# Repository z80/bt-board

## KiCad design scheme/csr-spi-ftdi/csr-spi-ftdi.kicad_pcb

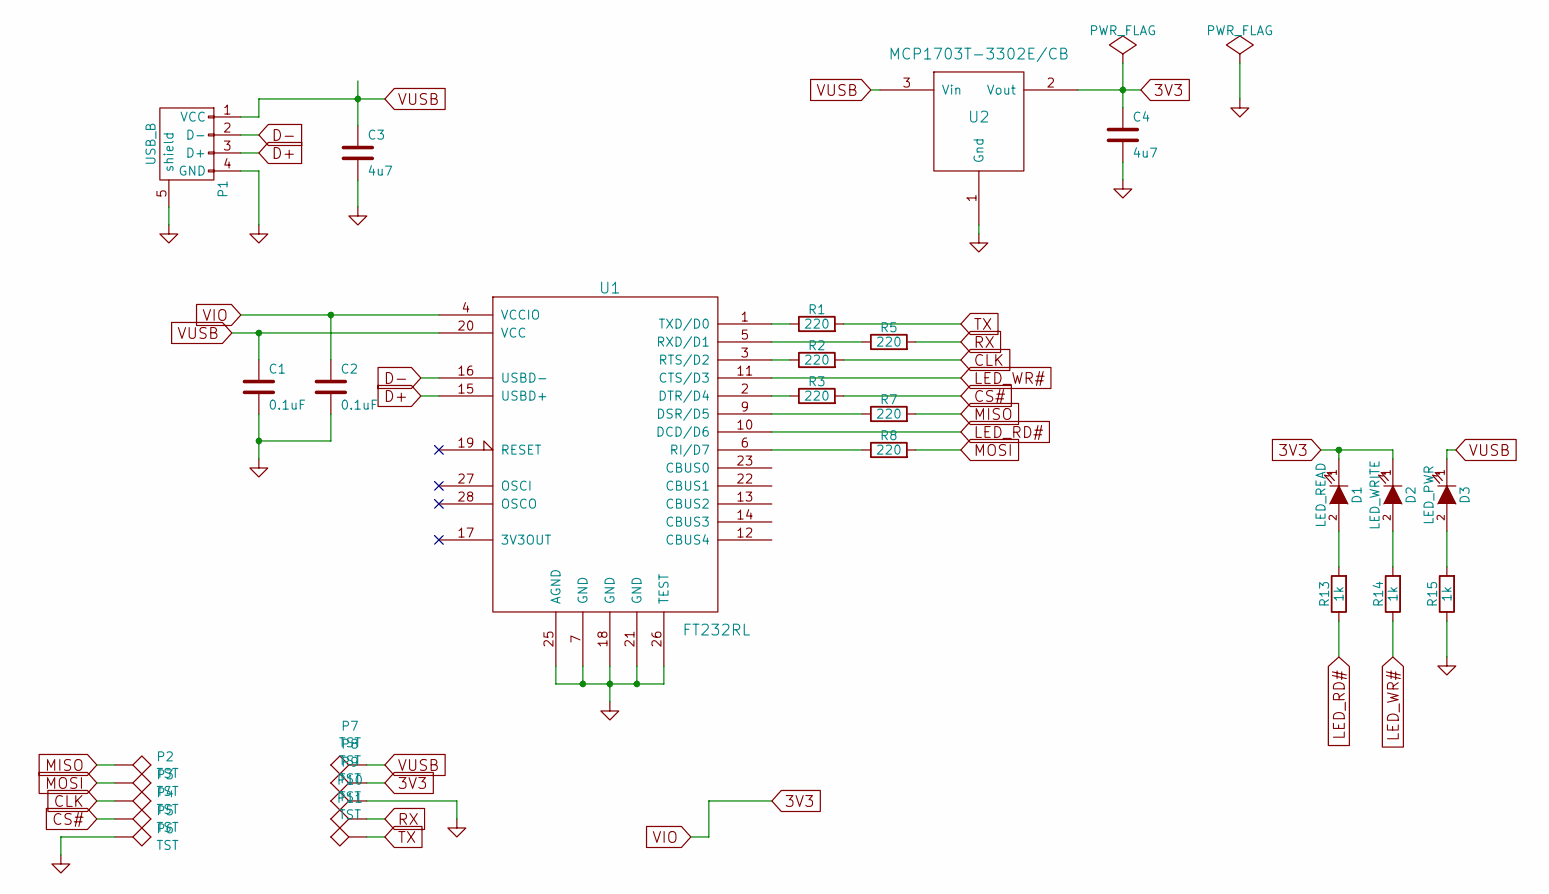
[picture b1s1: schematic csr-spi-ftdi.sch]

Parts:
C1, C2: 0.1uF; C_0805
C3, C4: 4u7; C_0805
D1: LED_READ; LED-5MM
D2: LED_WRITE; LED-5MM
D3: LED_PWR; LED-5MM
P1: USB_B
P2, P3, P4, P5, P6, P7, P8, P9, P10, P11: TST; Measurement_Point_Round-SMD-Pad_Small
R1, R2, R3, R5, R7, R8: 220; R_0805
R13, R14, R15: 1k; R_0805
U1: FT232RL; SSOP-28_5.3x10.2mm_Pitch0.65mm
U2: MCP1703T-3302E/CB; SOT-23_Handsoldering

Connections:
3V3: C2.1, C4.1, D1.1 (K), D2.1 (K), P8.1, U1.4 (VCCIO), U2.2 (Vout)
CLK: P4.1, R2.2
CS#: P5.1, R3.2
D+: P1.3 (D+), U1.15 (USBD+)
D-: P1.2 (D-), U1.16 (USBD-)
GND: C1.2, C2.2, C3.2, C4.2, P1.4 (GND), P1.5 (shield), P6.1, P9.1, R15.1, U1.7 (GND), U1.18 (GND), U1.21 (GND), U1.25 (AGND), U1.26 (TEST), U2.1 (Gnd)
LED_RD#: R13.1, U1.10 (DCD/D6)
LED_WR#: R14.1, U1.11 (CTS/D3)
MISO: P2.1, R7.2
MOSI: P3.1, R8.2
unnamed: D1.2 (A), R13.2
unnamed: D2.2 (A), R14.2
unnamed: D3.2 (A), R15.2
unnamed: R1.1, U1.1 (TXD/D0)
unnamed: R2.1, U1.3 (RTS/D2)
unnamed: R3.1, U1.2 (DTR/D4)
unnamed: R5.1, U1.5 (RXD/D1)
unnamed: R7.1, U1.9 (DSR/D5)
unnamed: R8.1, U1.6 (RI/D7)
RX: P10.1, R5.2
TX: P11.1, R1.2
VUSB: C1.1, C3.1, D3.1 (K), P1.1 (VCC), P7.1, U1.20 (VCC), U2.3 (Vin)

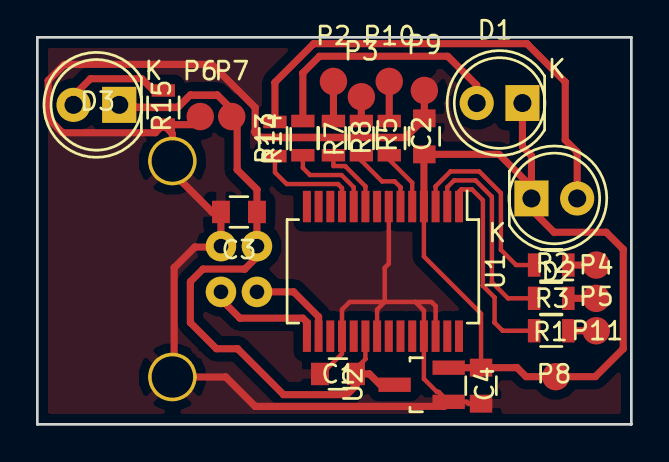
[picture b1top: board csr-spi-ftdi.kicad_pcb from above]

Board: 2 copper layers, 33.0 x 21.5 mm, 29 parts (1 on the bottom side), 22 nets.

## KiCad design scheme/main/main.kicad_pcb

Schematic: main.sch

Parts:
C1, C2: 18p
C3, C4, C6, C7, C8: 100n
C5, C10: 10u
C9: 100u
D1: LED
D2, D3: DIODE
J1: USB_A
K1: swd
P1: mode
P2: rst
P3, P5: CONN_20X2_F
P4, P7: CONN_20X2_M
P6: +
P8: -
R1: 100
R2, R3, R6, R7, R8, R9: 10k
R4, R5: 1k
R10: 100k
R11, R12: 22
R13: 1k5
U1: CRYSTAL-4PIN
U2: MCP1703T-3302E/CB
U3: MICRO-USB-B
stm1: STM32F102C8T6

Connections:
/Vin: D2.1 (A), P3.39, P3.40, P4.39, P4.40, P5.39, P5.40, P6.1, P7.39, P7.40
/Vusb: D3.1 (A), J1.1 (VCC), P3.37, P3.38, P4.37, P4.38, P5.37, P5.38, P7.37, P7.38, U3.1
/pa0: P3.3, P3.4, P4.3, P4.4, stm1.10 (PA0/WKUP/USART2_CTS/ADC_IN0/TIM2_CH1_ETR)
/pa1: P3.5, P3.6, P4.5, P4.6, stm1.11 (PA1/USART2_RTS/ADC_IN1/TIM2_CH2)
/pa2: P3.7, P3.8, P4.7, P4.8, stm1.12 (PA2/USART2_TX/ADC_IN2/TIM2_CH3)
/pa3: P3.9, P3.10, P4.9, P4.10, stm1.13 (PA3/USART2_RX/ADC_IN3/TIM2_CH4)
/pa4: P3.11, P3.12, P4.11, P4.12, stm1.14 (PA4/SPI1_NSS/ADC_IN4/USART2_CK)
/pa5: P3.13, P3.14, P4.13, P4.14, stm1.15 (PA5/SPI1_SCK/ADC_IN5)
/pa6: P3.15, P3.16, P4.15, P4.16, stm1.16 (PA6/SPI1_MISO/ADC_IN6/TIM3_CH1)
/pa7: P3.17, P3.18, P4.17, P4.18, stm1.17 (PA7/SPI1_MOSI/ADC_IN7/TIM3_CH2)
/pa8: P3.19, P3.20, P4.19, P4.20, stm1.29 (PA8/USART1_CK/MCO)
/pa9: P3.21, P3.22, P4.21, P4.22, stm1.30 (PA9/USART1_TX)
/pa10: P3.23, P3.24, P4.23, P4.24, stm1.31 (PA10/USART1_RX)
/pa15: P3.25, P3.26, P4.25, P4.26, stm1.38 (JDI^TIM2_CH1_ETR/PA15/SPI1_NSS)
/pb0: P3.27, P3.28, P4.27, P4.28, stm1.18 (PB0/ADC_IN8/TIM3_CH3)
/pb3: P3.29, P3.30, P4.29, P4.30, stm1.39 (JTDO^TIM2_CH2/PB3/TRACESWO/SPI1_SCKPB3)
/pb4: P3.31, P3.32, P4.31, P4.32, stm1.40 (JNTRST^TIM3_CH1/PB4/SPI1_MISO)
/pb5: P5.7, P5.8, P7.7, P7.8, stm1.41 (PB5/I2C1_SMBA^TIM3_CH2/SPI1_MOSI)
/pb6-scl1: P5.3, P5.4, P7.3, P7.4, R6.2, stm1.42 (PB6/I2C1_SCL/TIM4_CH1^USART1_TX)
/pb7-sda1: P5.5, P5.6, P7.5, P7.6, R7.2, stm1.43 (PB7/I2C1_SDA/TIM4_CH3^USART1_RX)
/pb8: P5.15, P5.16, P7.15, P7.16, stm1.45 (PB8/TIM4_CH3^I2C1_SCL)
/pb9: P5.17, P5.18, P7.17, P7.18, stm1.46 (PB9/TIM4_CH4^I2C1_SDA)
/pb10-scl2: P5.11, P5.12, P7.11, P7.12, R8.2, stm1.21 (PB10/I2C2_SCL/USART3_TX^TIM2_CH3)
/pb11-sda2: P5.13, P5.14, P7.13, P7.14, R9.2, stm1.22 (PB11/I2C2_SDA/USART3_RX^TIM2_CH4)
/pb12: P5.19, P5.20, P7.19, P7.20, stm1.25 (PB12/SPI2_NSS/I2C2_SMBA/USART3_CTS)
/pb13: P5.21, P5.22, P7.21, P7.22, stm1.26 (PB13/SPI2_SCK/USART3_CTS)
/pb14: P5.23, P5.24, P7.23, P7.24, stm1.27 (PB14/SPI2_MISO/USART3_RTS)
/pb15: P5.25, P5.26, P7.25, P7.26, stm1.28 (PB15/SPI2_MOSI)
/pc13: P5.27, P5.28, P7.27, P7.28, stm1.2 (PC13/TAMPER-RTC)
/pc14: P5.29, P5.30, P7.29, P7.30, stm1.3 (PC14/OSC32_IN)
/pc15: P5.31, P5.32, P7.31, P7.32, stm1.4 (PC15/OSC32_OUT)
/swd-clk: K1.3, stm1.37 (JTCK/SWCLK^PA14)
/swd-io: K1.1, stm1.34 (JTMS/SWDIO^PA13)
/usb-conn: R13.2, stm1.20 (PB2/BOOT1)
/usb-d+: R12.1, stm1.33 (PA12/USART1_RTS/USBDP)
/usb-d-: R11.1, stm1.32 (PA11/USART1_CTS/USBDM)
GND: C1.1, C2.1, C3.2, C4.1, C5.2, C6.2, C7.2, C8.2, C9.2, C10.2, D1.2 (K), J1.4 (GND), K1.2 (PM), P2.2 (PM), P3.1, P3.2, P3.33, P3.34, P4.1, P4.2, P4.33, P4.34, P5.1, P5.2, P5.9, P5.10, P5.33, P5.34, P7.1, P7.2, P7.9, P7.10, P7.33, P7.34, P8.1, R2.2, R10.2, U1.2, U1.4, U2.1 (Gnd), U3.5, U3.6, U3.7, U3.8, U3.9, stm1.8 (Vssa), stm1.23 (Vss_1), stm1.35 (Vss_2), stm1.47 (Vss_3)
unnamed: R10.1, U3.4
unnamed: D1.1 (A), R5.2
unnamed: R11.2, U3.2
unnamed: R12.2, R13.1, U3.3
unnamed: P1.2 (PM), R2.1, stm1.44 (BOOT0)
unnamed: R5.1, stm1.19 (PB1/ADC_IN9/TIM3_CH4)
unnamed: R1.2, stm1.6 (PD1/OSC_OUT)
unnamed: C4.2, P2.1, R3.2, stm1.7 (NRST)
unnamed: C9.1, D2.2 (K), D3.2 (K), U2.3 (Vin)
unnamed: C2.2, R1.1, U1.1
unnamed: C1.2, U1.3, stm1.5 (PD0/OSC_IN)
unnamed: C3.1, C5.1, R4.2, stm1.9 (Vdda)
VDD: C6.1, C7.1, C8.1, C10.1, P1.1, P3.35, P3.36, P4.35, P4.36, P5.35, P5.36, P7.35, P7.36, R3.1, R4.1, R6.1, R7.1, R8.1, R9.1, U2.2 (Vout), stm1.1 (Vbat), stm1.24 (Vdd_1), stm1.36 (Vdd_2), stm1.48 (Vdd_3)

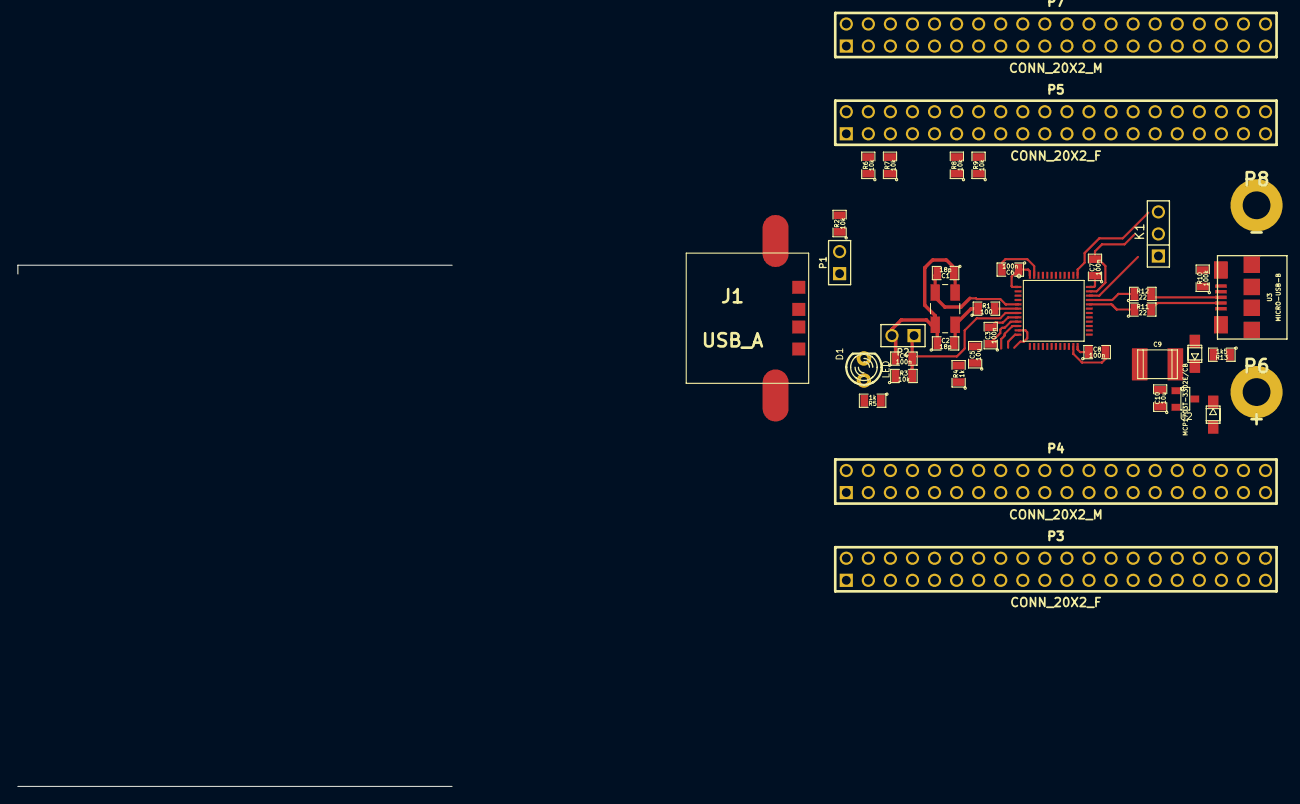
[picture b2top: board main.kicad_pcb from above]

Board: 2 copper layers, 40 parts (0 on the bottom side), 50 nets.

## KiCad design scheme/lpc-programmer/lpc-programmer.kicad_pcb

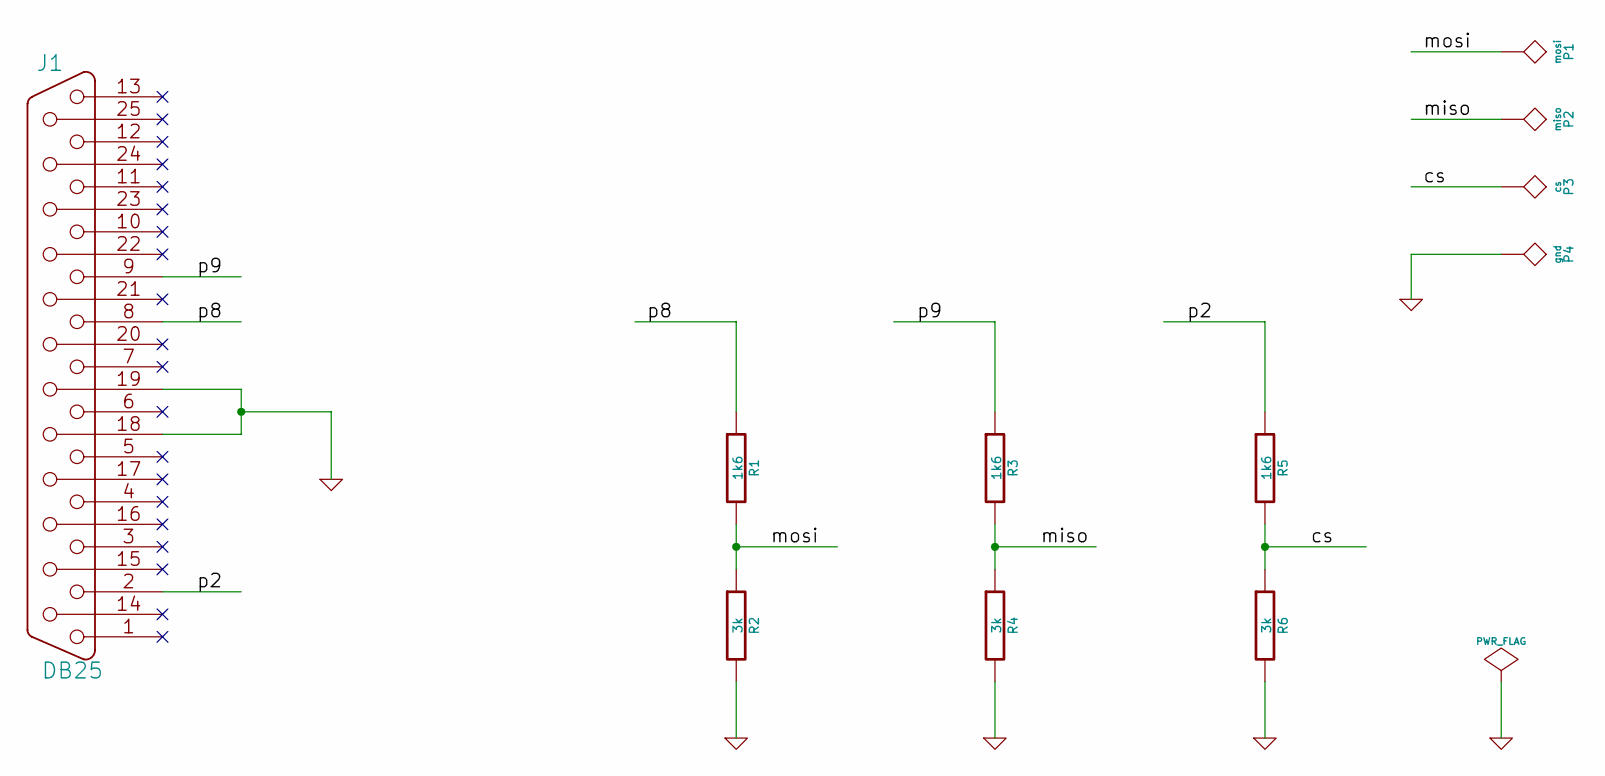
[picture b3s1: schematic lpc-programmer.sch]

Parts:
J1: DB25
P1: mosi
P2: miso
P3: cs
P4: gnd
R1, R3, R5: 1k6
R2, R4, R6: 3k

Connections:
/cs: P3.1, R5.2, R6.1
/miso: P2.1, R3.2, R4.1
/mosi: P1.1, R1.2, R2.1
/p2: J1.2, R5.1
/p8: J1.8, R1.1
/p9: J1.9, R3.1
GND: J1.18, J1.19, P4.1, R2.2, R4.2, R6.2

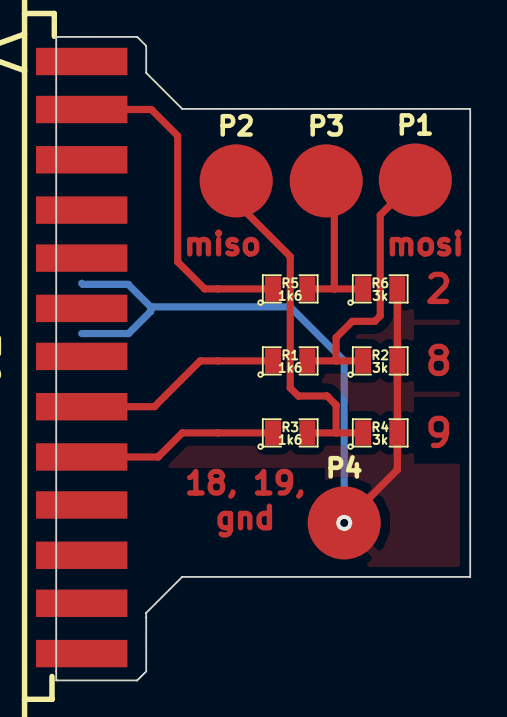
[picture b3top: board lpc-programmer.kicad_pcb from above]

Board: 2 copper layers, 23.0 x 35.8 mm, 11 parts (0 on the bottom side), 7 nets.

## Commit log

2014-09-04 Copied chibios-2.6.4.
2014-09-04 Renamed folder.
2014-09-26 Firmware compiles.
2014-09-26 Discovery value line.
2014-09-26 HC-05 documentation.
2014-09-26 Compiles.
2014-10-11 qextserial
2014-10-21 Chip datasheet. With SPI explanation.
2014-12-05 libs
2015-12-19 Copied needed libraries.
2015-12-19 Crosscompiled library.
2015-12-24 Added source libftdi-0.20.
2015-12-24 Modified ".gitignore".
2015-12-24 libftdi compiles. usbspi diesn't.
2015-12-24 Fixing troubles.
2015-12-24 Added ROOT directory variable.
2015-12-27 Started designing FTDI-RL board design.
2015-12-27 Assigned footprints to components.
2015-12-29 Finished debug PCB.
2016-01-26 Working binaries and code snapshot. Tested. Managed to read firmware and write firmware.
